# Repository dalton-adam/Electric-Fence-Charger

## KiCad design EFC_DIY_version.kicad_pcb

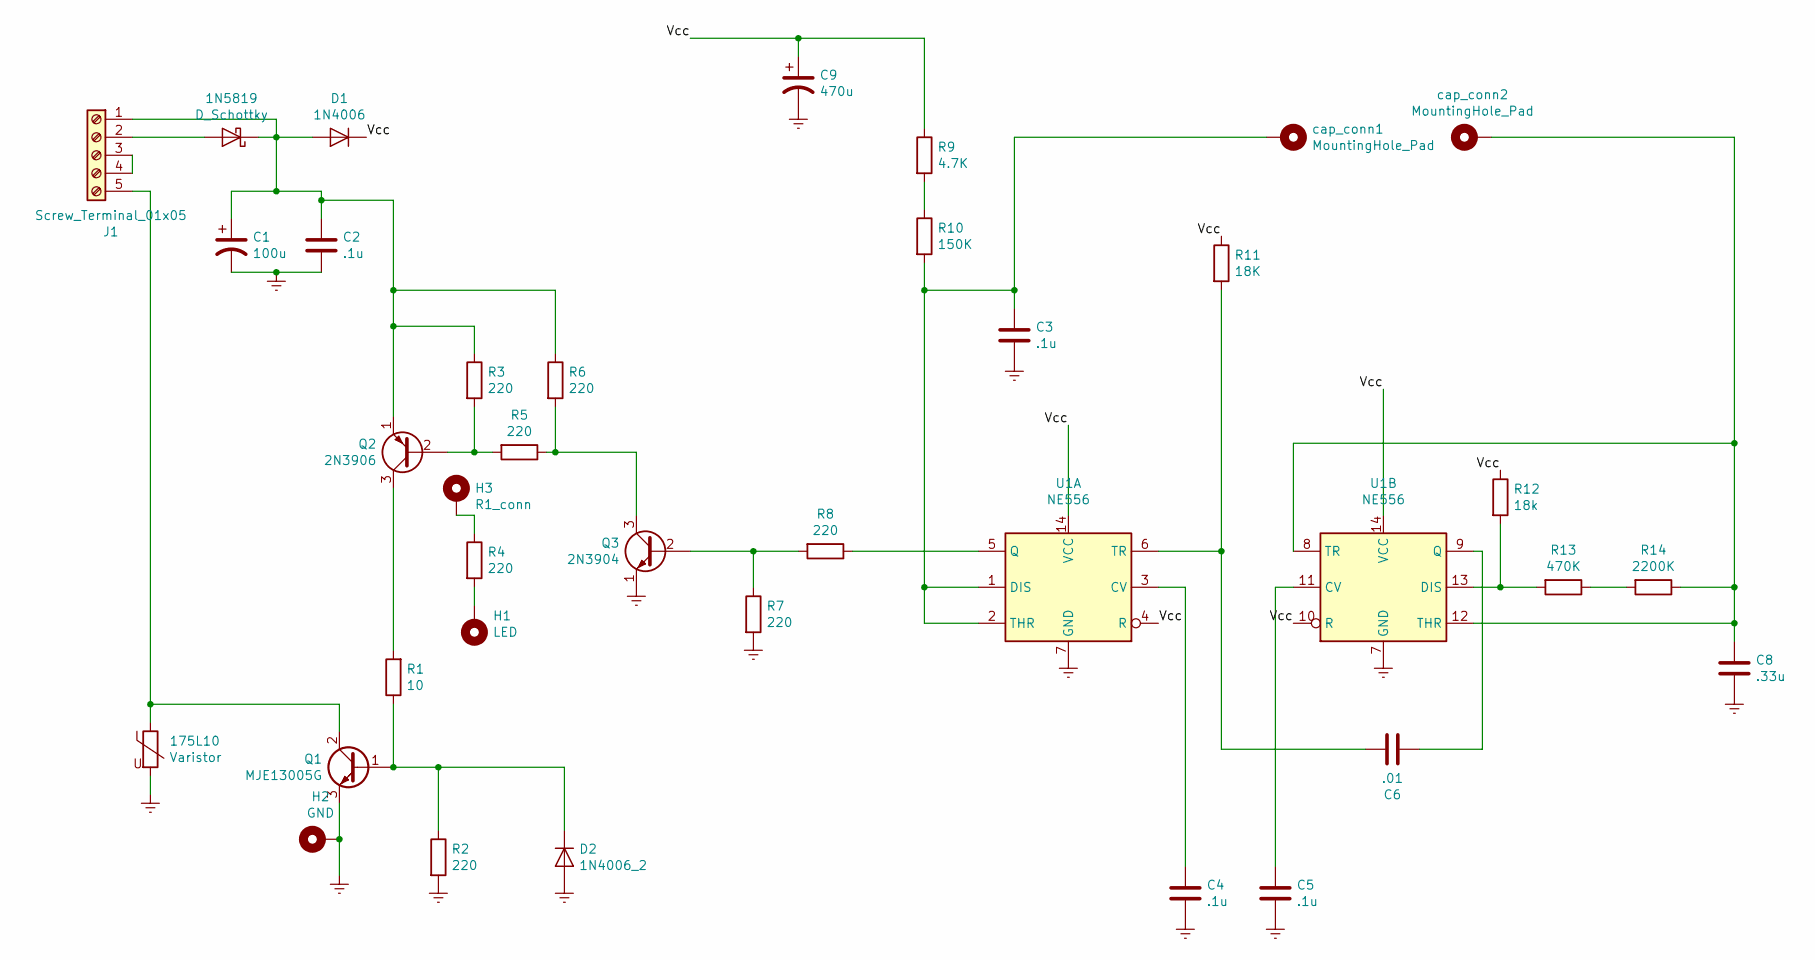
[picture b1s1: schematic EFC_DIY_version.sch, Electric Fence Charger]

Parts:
1N5819: D_Schottky; D_DO-15_P12.70mm_Horizontal
175L10: Varistor; RV_Disc_D15.5mm_W3.9mm_P7.5mm
C1: 100u; CP_Radial_D5.0mm_P2.50mm
C2, C3, C4, C5: .1u; C_Rect_L13.0mm_W4.0mm_P10.00mm_FKS3_FKP3_MKS4
C6: .01; C_Axial_L3.8mm_D2.6mm_P7.50mm_Horizontal
C8: .33u; C_Rect_L18.0mm_W5.0mm_P15.00mm_FKS3_FKP3
C9: 470u; CP_Radial_D8.0mm_P3.80mm
D1: 1N4006; D_DO-41_SOD81_P10.16mm_Horizontal
D2: 1N4006_2; D_DO-41_SOD81_P10.16mm_Horizontal
H1: LED; MountingHole_2.2mm_M2_ISO14580_Pad
H2: GND; MountingHole_2.2mm_M2_ISO14580_Pad
H3: R1_conn; MountingHole_2.2mm_M2_ISO14580_Pad
J1: Screw_Terminal_01x05; TerminalBlock_RND_205-00235_1x05_P5.08mm_Horizontal
Q1: MJE13005G; TO-220-3_Vertical
Q2: 2N3906; TO-92L_Inline_Wide
Q3: 2N3904; TO-92L_Inline_Wide
R1: 10; R_Axial_DIN0411_L9.9mm_D3.6mm_P12.70mm_Horizontal
R2, R3, R4, R5, R6, R7, R8: 220; R_Axial_DIN0411_L9.9mm_D3.6mm_P12.70mm_Horizontal
R9: 4.7K; R_Axial_DIN0411_L9.9mm_D3.6mm_P12.70mm_Horizontal
R10: 150K; R_Axial_DIN0411_L9.9mm_D3.6mm_P12.70mm_Horizontal
R11: 18K; R_Axial_DIN0411_L9.9mm_D3.6mm_P12.70mm_Horizontal
R12: 18k; R_Axial_DIN0411_L9.9mm_D3.6mm_P12.70mm_Horizontal
R13: 470K; R_Axial_DIN0411_L9.9mm_D3.6mm_P12.70mm_Horizontal
R14: 2200K; R_Axial_DIN0411_L9.9mm_D3.6mm_P12.70mm_Horizontal
U1: NE556; DIP-14_W7.62mm_Socket_LongPads
cap_conn1, cap_conn2: MountingHole_Pad; MountingHole_2.2mm_M2_ISO14580_Pad

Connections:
/Vcc: C9.1, D1.1 (K), R9.1, R11.1, R12.1, U1.4 (R), U1.10 (R), U1.14 (VCC)
Earth: 175L10.2, C1.2, C2.2, C3.2, C4.2, C5.2, C8.2, C9.2, D2.2 (A), H2.1, Q1.3 (E), Q3.1 (E), R2.2, R7.2, U1.7 (GND)
unnamed: 1N5819.1 (K), C1.1, C2.1, D1.2 (A), J1.1, Q2.1 (E), R3.1, R6.1
unnamed: 1N5819.2 (A), J1.2
unnamed: 175L10.1, J1.5, Q1.2 (C)
unnamed: C3.1, R10.2, U1.1 (DIS), U1.2 (THR), cap_conn1.1
unnamed: C4.1, U1.3 (CV)
unnamed: C5.1, U1.11 (CV)
unnamed: C6.1, R11.2, U1.6 (TR)
unnamed: C6.2, U1.9 (Q)
unnamed: C8.1, R14.1, U1.8 (TR), U1.12 (THR), cap_conn2.1
unnamed: D2.1 (K), Q1.1 (B), R1.1, R2.1
unnamed: H1.1, R4.2
unnamed: H3.1, R4.1
unnamed: J1.3, J1.4
unnamed: Q2.2 (B), R3.2, R5.2
unnamed: Q2.3 (C), R1.2
unnamed: Q3.2 (B), R7.1, R8.2
unnamed: Q3.3 (C), R5.1, R6.2
unnamed: R8.1, U1.5 (Q)
unnamed: R9.2, R10.1
unnamed: R12.2, R13.2, U1.13 (DIS)
unnamed: R13.1, R14.2

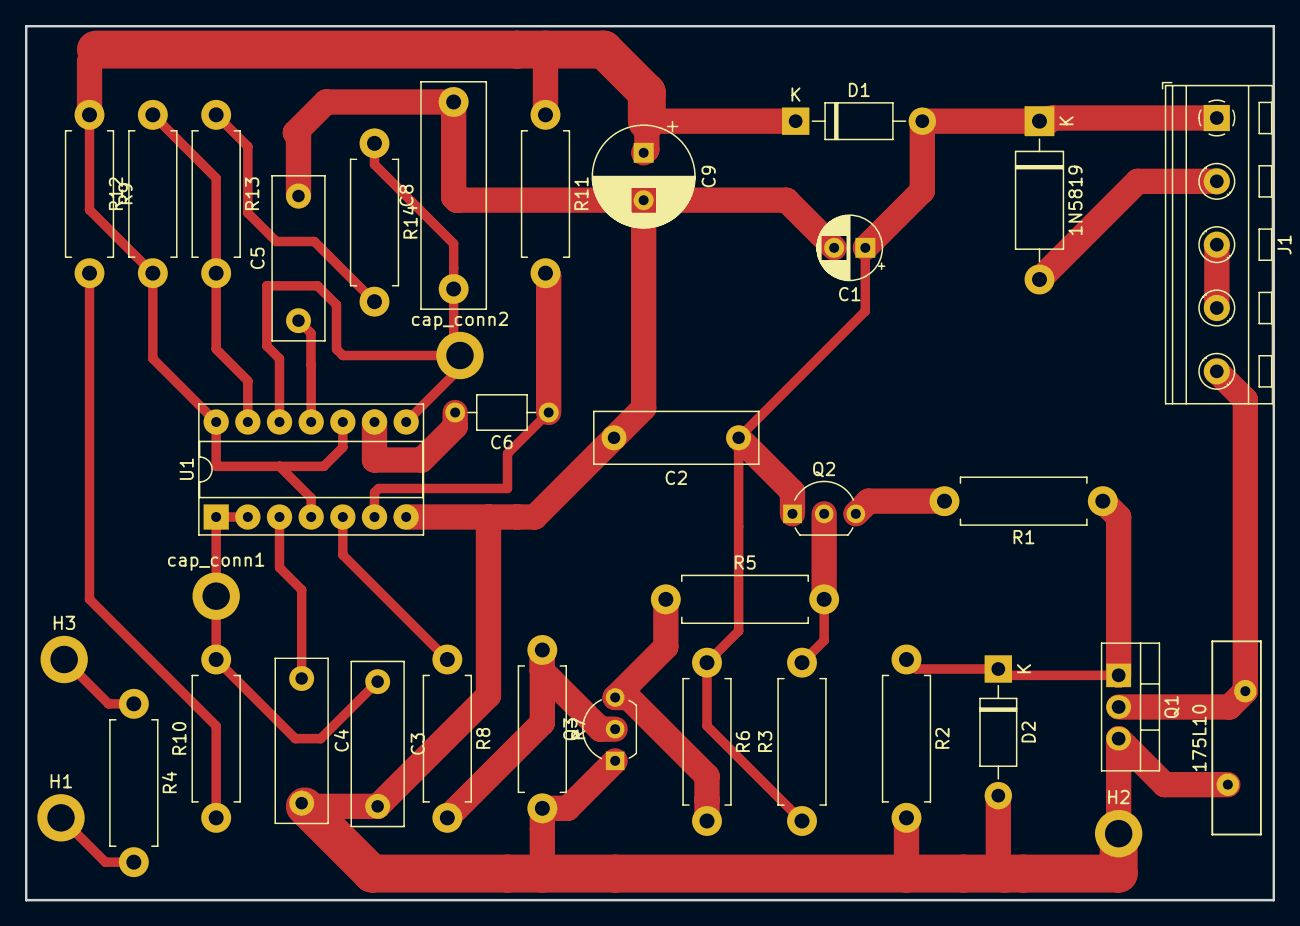
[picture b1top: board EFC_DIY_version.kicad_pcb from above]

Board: 2 copper layers, 100.1 x 70.1 mm, 36 parts (0 on the bottom side), 23 nets.

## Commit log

2020-04-22 Added Kicad digikey libraries and a partial SMD schematic for charger.
2020-04-22 Updated with thicker trace widths.
2020-04-23 Corrected Diode polarity
2020-05-01 Various Changes
